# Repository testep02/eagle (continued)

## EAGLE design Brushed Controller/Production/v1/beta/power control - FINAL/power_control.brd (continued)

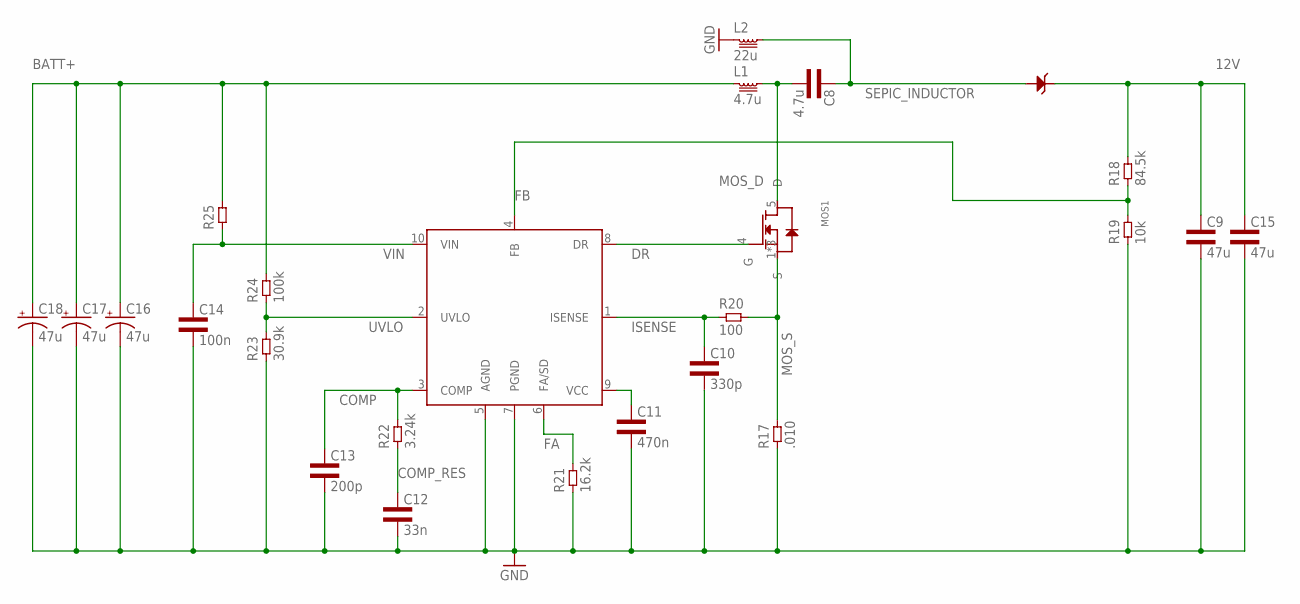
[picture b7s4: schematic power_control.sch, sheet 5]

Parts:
C8: 4.7u; 1206L3
C9, C15: 47u; 1210L3
C10: 330p; 0402L3
C11: 470n; 0402L3
C12: 33n; 0402L3
C13: 200p; 0402L3
C14: 100n; 0603L3
C16, C17, C18: 47u; CT7343
D3: SCHOTTKYDIODEDPAK; DPAK
L1: 4.7u; SRP6540
L2: 22u; IHLP3232DZ11
MOS1: MOSFET-NPG-TDSON-8; PG-TDSON-8
R17: .010; 1206L3
R18: 84.5k; 0402L3
R19: 10k; 0402L3
R20: 100; 0402L3
R21: 16.2k; 0402L3
R22: 3.24k; 0402L3
R23: 30.9k; 0402L3
R24: 100k; 0402L3
R25: RES0402L3; 0402L3
U3: LM3481; S-PDSO-G10

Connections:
12V: C9.P$1 (1), C15.P$1 (1), D3.TAB (CATHODE), R18.P$2 (2); also elsewhere on the board
BATT+: C16.+, C17.+, C18.+, L1.1, R24.P$2 (2), R25.P$2 (2)
COMP: C13.P$1 (1), R22.P$2 (2), U3.3 (COMP)
COMP_RES: C12.P$1 (1), R22.P$1 (1)
DR: MOS1.4 (G), U3.8 (DR)
FA: R21.P$2 (2), U3.6 (FA/SD)
FB: R18.P$1 (1), R19.P$2 (2), U3.4 (FB)
GND: C9.P$2 (2), C10.P$2 (2), C11.P$2 (2), C12.P$2 (2), C13.P$2 (2), C14.P$2 (2), C15.P$2 (2), C16.-, C17.-, C18.-, L2.1, R17.1, R19.P$1 (1), R21.P$1 (1), R23.P$1 (1), U3.5 (AGND), U3.7 (PGND); also elsewhere on the board
ISENSE: C10.P$1 (1), R20.P$1 (1), U3.1 (ISENSE)
MOS_D: C8.2, L1.2, MOS1.5 (D)
MOS_S: MOS1.1 (S), MOS1.2 (S), MOS1.3 (S), R17.2, R20.P$2 (2)
unnamed: C11.P$1 (1), U3.9 (VCC)
SEPIC_INDUCTOR: C8.1, D3.1 (ANODE), D3.3 (ANODE), L2.2
UVLO: R23.P$2 (2), R24.P$1 (1), U3.2 (UVLO)
VIN: C14.P$1 (1), R25.P$1 (1), U3.10 (VIN)

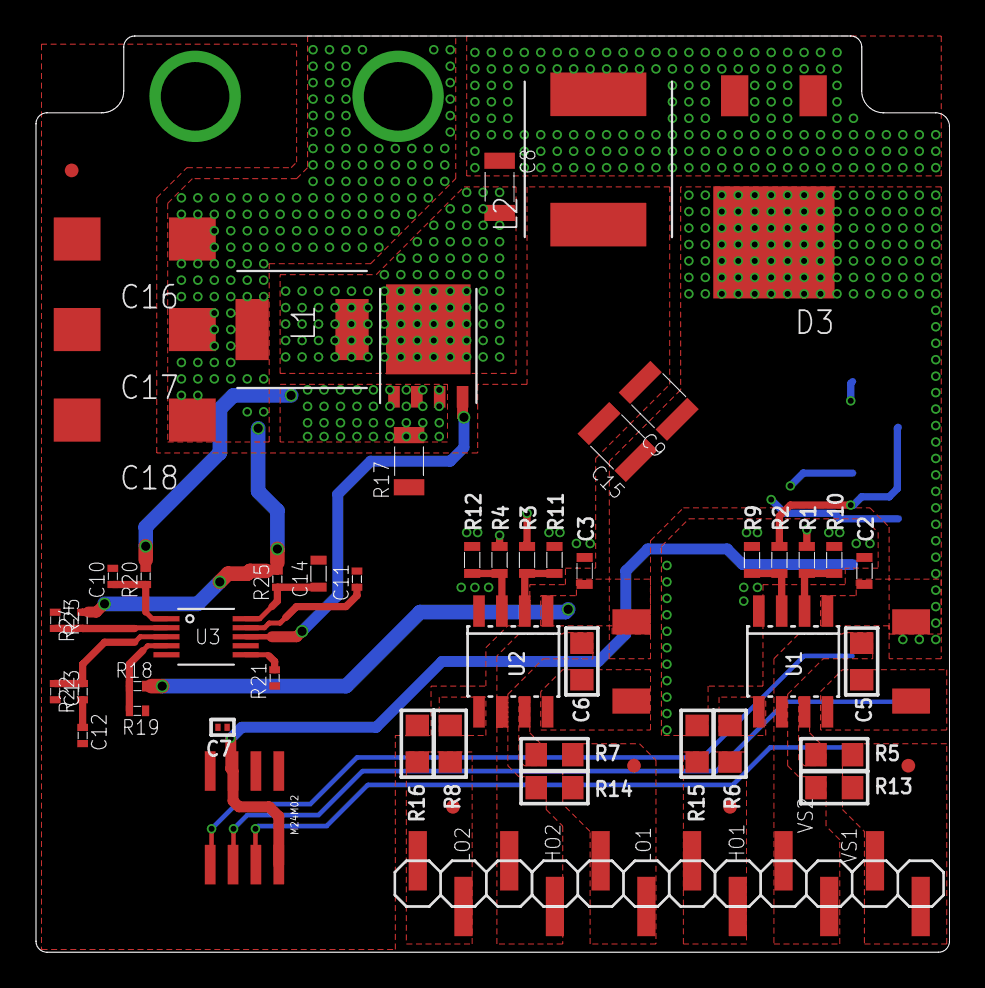
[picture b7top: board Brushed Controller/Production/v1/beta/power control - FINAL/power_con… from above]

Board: 4 copper layers, 50.7 x 50.9 mm, 58 parts (1 on the bottom side), 39 nets.
